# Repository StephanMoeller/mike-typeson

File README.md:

# Mike Typeson
He is not pretty, but he gets the job done.

This is my first keyboard that has a home grown pcb. It is wired as a unibody even though the electronics are in 3 pieces. I made it because I needed a simple keyboard that did not require i2c, to test out my custom firmware found here: https://github.com/StephanMoeller/zigmkay

An stl can be found directly in this repo (mike-typeson.stl)

To build this, the following things are needed:

- 3d printed case
- PCB
- THT diodes (30 pieces)
- Khailh mx sockets (30 pieces)
- A xiao rp2040 microcontroller
- 16 jumper wires with female dupont in both ends

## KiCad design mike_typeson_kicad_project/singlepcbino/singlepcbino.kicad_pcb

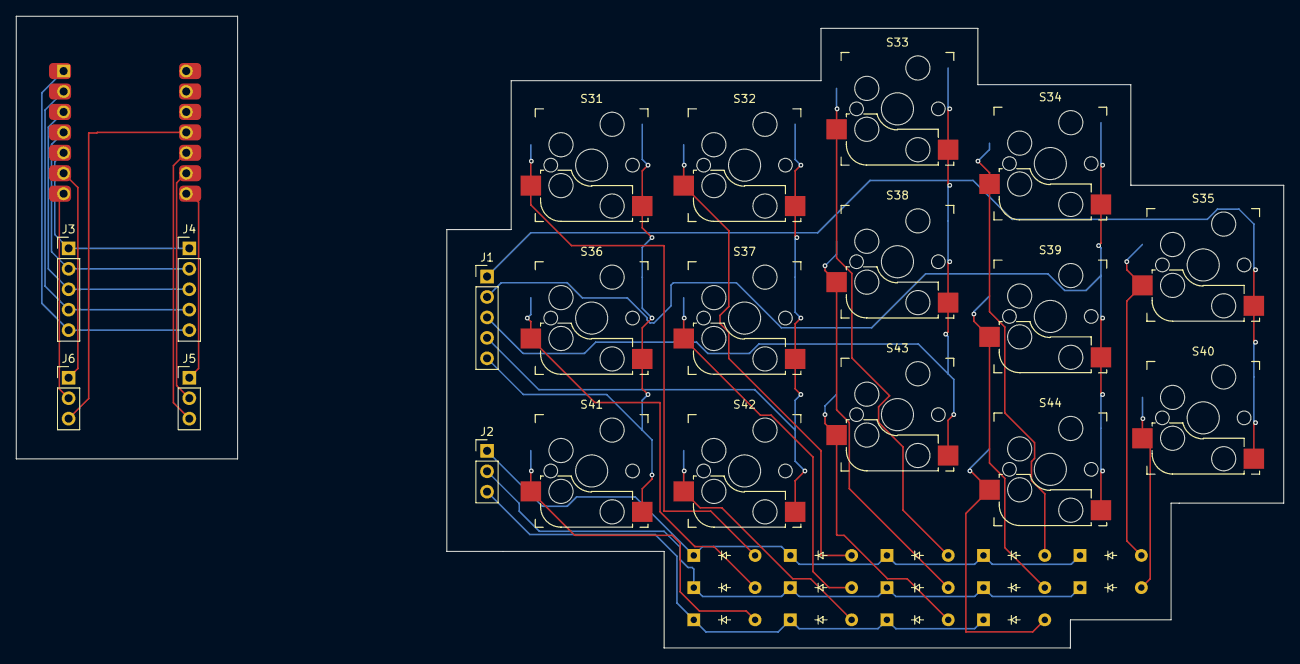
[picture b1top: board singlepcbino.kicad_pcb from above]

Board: 2 copper layers, 157.5 x 78.5 mm, 35 parts (0 on the bottom side), 33 nets.

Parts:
J1, J3, J4: Conn_01x05; PinHeader_1x05_P2.54mm_Vertical
J2, J5, J6: Conn_01x03; PinHeader_1x03_P2.54mm_Vertical
S31: a40; Kailh_socket_MX_reversible
S32: a30; Kailh_socket_MX_reversible
S33: a20; Kailh_socket_MX_reversible
S34: a10; Kailh_socket_MX_reversible
S35: a00; Kailh_socket_MX_reversible
S36: a41; Kailh_socket_MX_reversible
S37: a31; Kailh_socket_MX_reversible
S38: a21; Kailh_socket_MX_reversible
S39: a11; Kailh_socket_MX_reversible
S40: a01; Kailh_socket_MX_reversible
S41: a42; Kailh_socket_MX_reversible
S42: a32; Kailh_socket_MX_reversible
S43: a22; Kailh_socket_MX_reversible
S44: a12; Kailh_socket_MX_reversible
U1: MCU_Seeed_XIAO_RP2040; Seeed_XIAO_RP2040
a00, a01, a10, a11, a12, a20, a21, a22, a30, a31, a32, a40, a41, a42: Diode; Diode_DO-35

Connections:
/col0: J1.5, S31.1, S36.1, S41.1
/col1: J1.4, S32.1, S37.1, S42.1
/col2: J1.3, S33.1, S38.1, S43.1
/col3: J1.2, S34.1, S39.1, S44.1
/col4: J1.1, S35.1, S40.1
/row0: J2.1, a00.1 (K), a10.1 (K), a20.1 (K), a30.1 (K), a40.1 (K)
/row1: J2.2, a01.1 (K), a11.1 (K), a21.1 (K), a31.1 (K), a41.1 (K)
unnamed: J2.3, a12.1 (K), a22.1 (K), a32.1 (K), a42.1 (K)
unnamed: J3.1, J4.1, U1.5 (PA8_A4_D4_SDA)
unnamed: J3.2, J4.2, U1.4 (PA11_A3_D3)
unnamed: J3.3, J4.3, U1.3 (PA10_A2_D2)
unnamed: J3.4, J4.4, U1.2 (PA4_A1_D1)
unnamed: J3.5, J4.5, U1.1 (PA02_A0_D0)
unnamed: J5.1, U1.8 (PB09_A7_D7_RX)
unnamed: J5.2, U1.9 (PA7_A8_D8_SCK)
unnamed: J5.3, U1.10 (PA5_A9_D9_MISO)
unnamed: J6.1, U1.6 (PA9_A5_D5_SCL)
unnamed: J6.2, U1.7 (PB08_A6_D6_TX)
unnamed: J6.3, U1.11 (PA6_A10_D10_MOSI)
unnamed: S35.2, a00.2 (A)
unnamed: S40.2, a01.2 (A)
unnamed: S34.2, a10.2 (A)
unnamed: S39.2, a11.2 (A)
unnamed: S44.2, a12.2 (A)
unnamed: S33.2, a20.2 (A)
unnamed: S38.2, a21.2 (A)
unnamed: S43.2, a22.2 (A)
unnamed: S32.2, a30.2 (A)
unnamed: S37.2, a31.2 (A)
unnamed: S42.2, a32.2 (A)
unnamed: S31.2, a40.2 (A)
unnamed: S36.2, a41.2 (A)
unnamed: S41.2, a42.2 (A)

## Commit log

2025-08-20 added resources
2025-08-20 readme done
